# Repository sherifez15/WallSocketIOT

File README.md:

# WallSocketIOT
This project is the electrical circuit design for a smart wall socket that communicates over WIFI
  
This project uses esp8266 Microchip to handle the logic between hardware and WifiController  
Desgined and assembled by: Sherif Gobran

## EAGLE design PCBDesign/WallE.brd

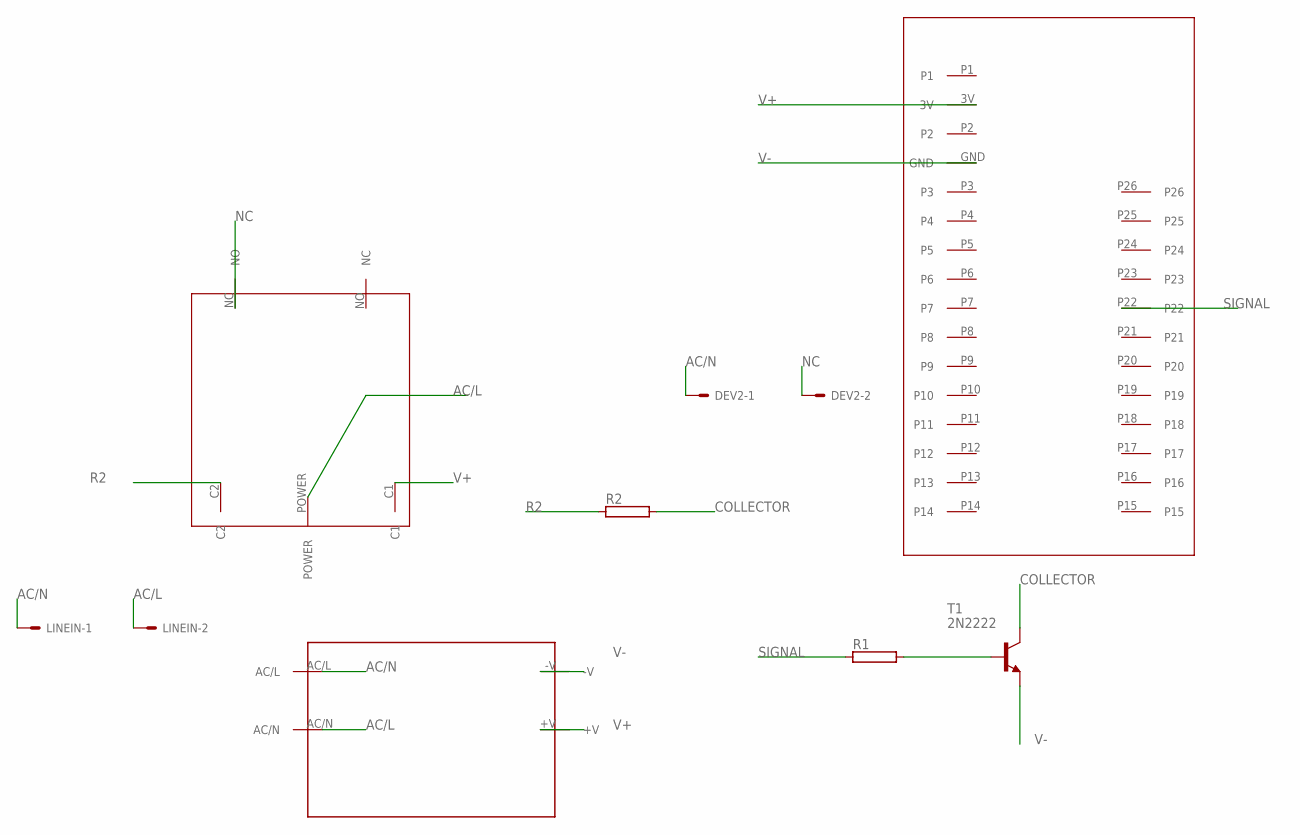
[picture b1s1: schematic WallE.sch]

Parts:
DEV2: dev1; 332-02
LINEIN: AC/L; 332-02
R1, R2: RMG100-V; TO-247-2V
T1: 2N2222; TO18
U$1: POWER_COMPONENT
U$2: 3VUXCELLCOIL; 3VUXCELLRELAY
U$3: ESP8266

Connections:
AC/L: LINEIN.2, U$1.AC/N, U$2.POWER
AC/N: DEV2.1, LINEIN.1, U$1.AC/L
COLLECTOR: R2.2, T1.3 (C)
unnamed: R1.2, T1.2 (B)
NC: DEV2.2, U$2.NC (NO)
R2: R2.1, U$2.C2
SIGNAL: R1.1, U$3.P22
V+: U$1.+V, U$2.C1, U$3.3V
V-: T1.1 (E), U$1.-V, U$3.GND

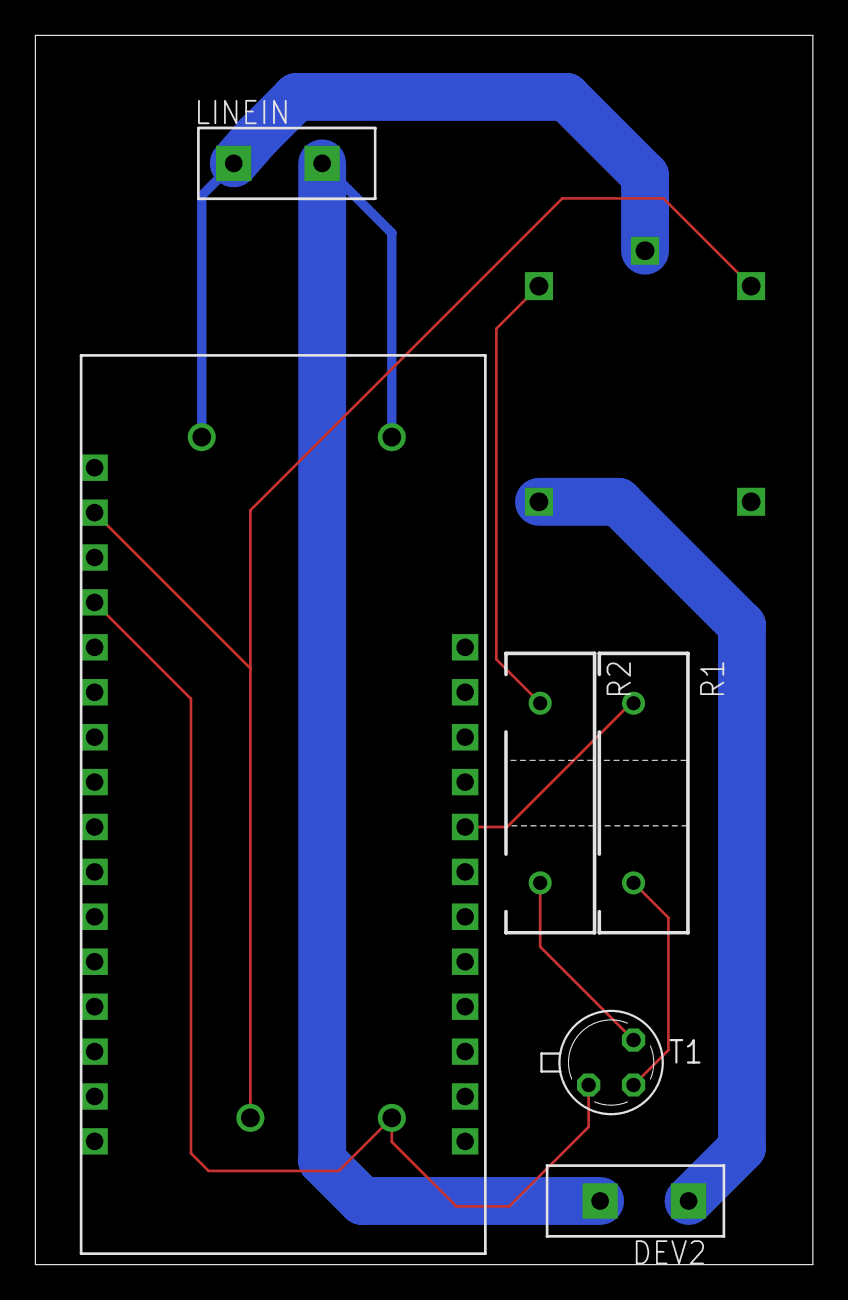
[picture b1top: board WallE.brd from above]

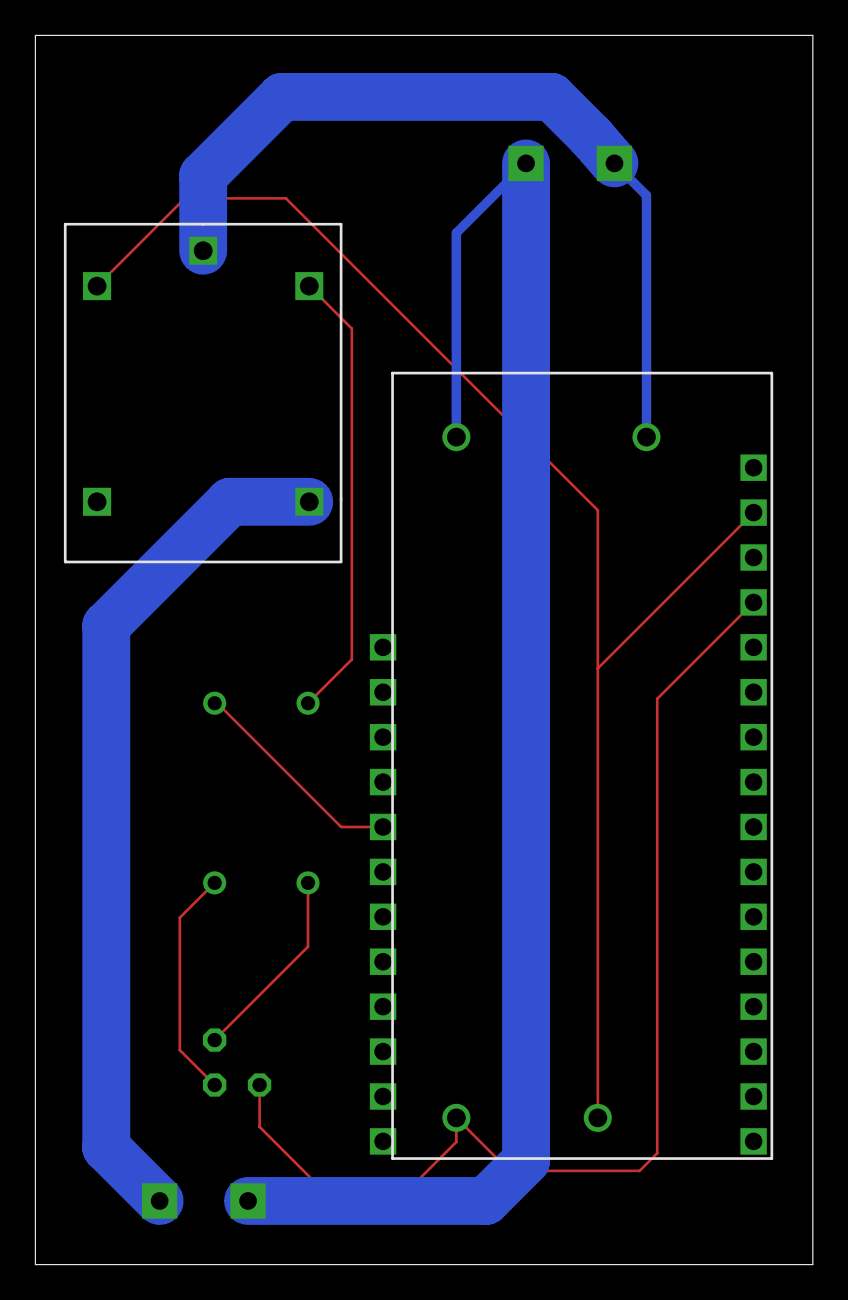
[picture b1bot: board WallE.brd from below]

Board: 2 copper layers, 44.0 x 69.5 mm, 8 parts (2 on the bottom side), 9 nets.

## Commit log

2020-06-20 InitialUpload
